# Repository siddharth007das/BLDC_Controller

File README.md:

# BLDC_Controller
A 50V 3Phase BLDC Controller Board designed to implement FoC Control of Hall Effect BLDC Motors such as NEMA17 24V 4000RPM. Utilizes Automotive grade Onsemi NFVA35065L32 Inverter ICs and STM32F4 to invert DC supply and perform Current and Voltage Measurement for FOC Control.

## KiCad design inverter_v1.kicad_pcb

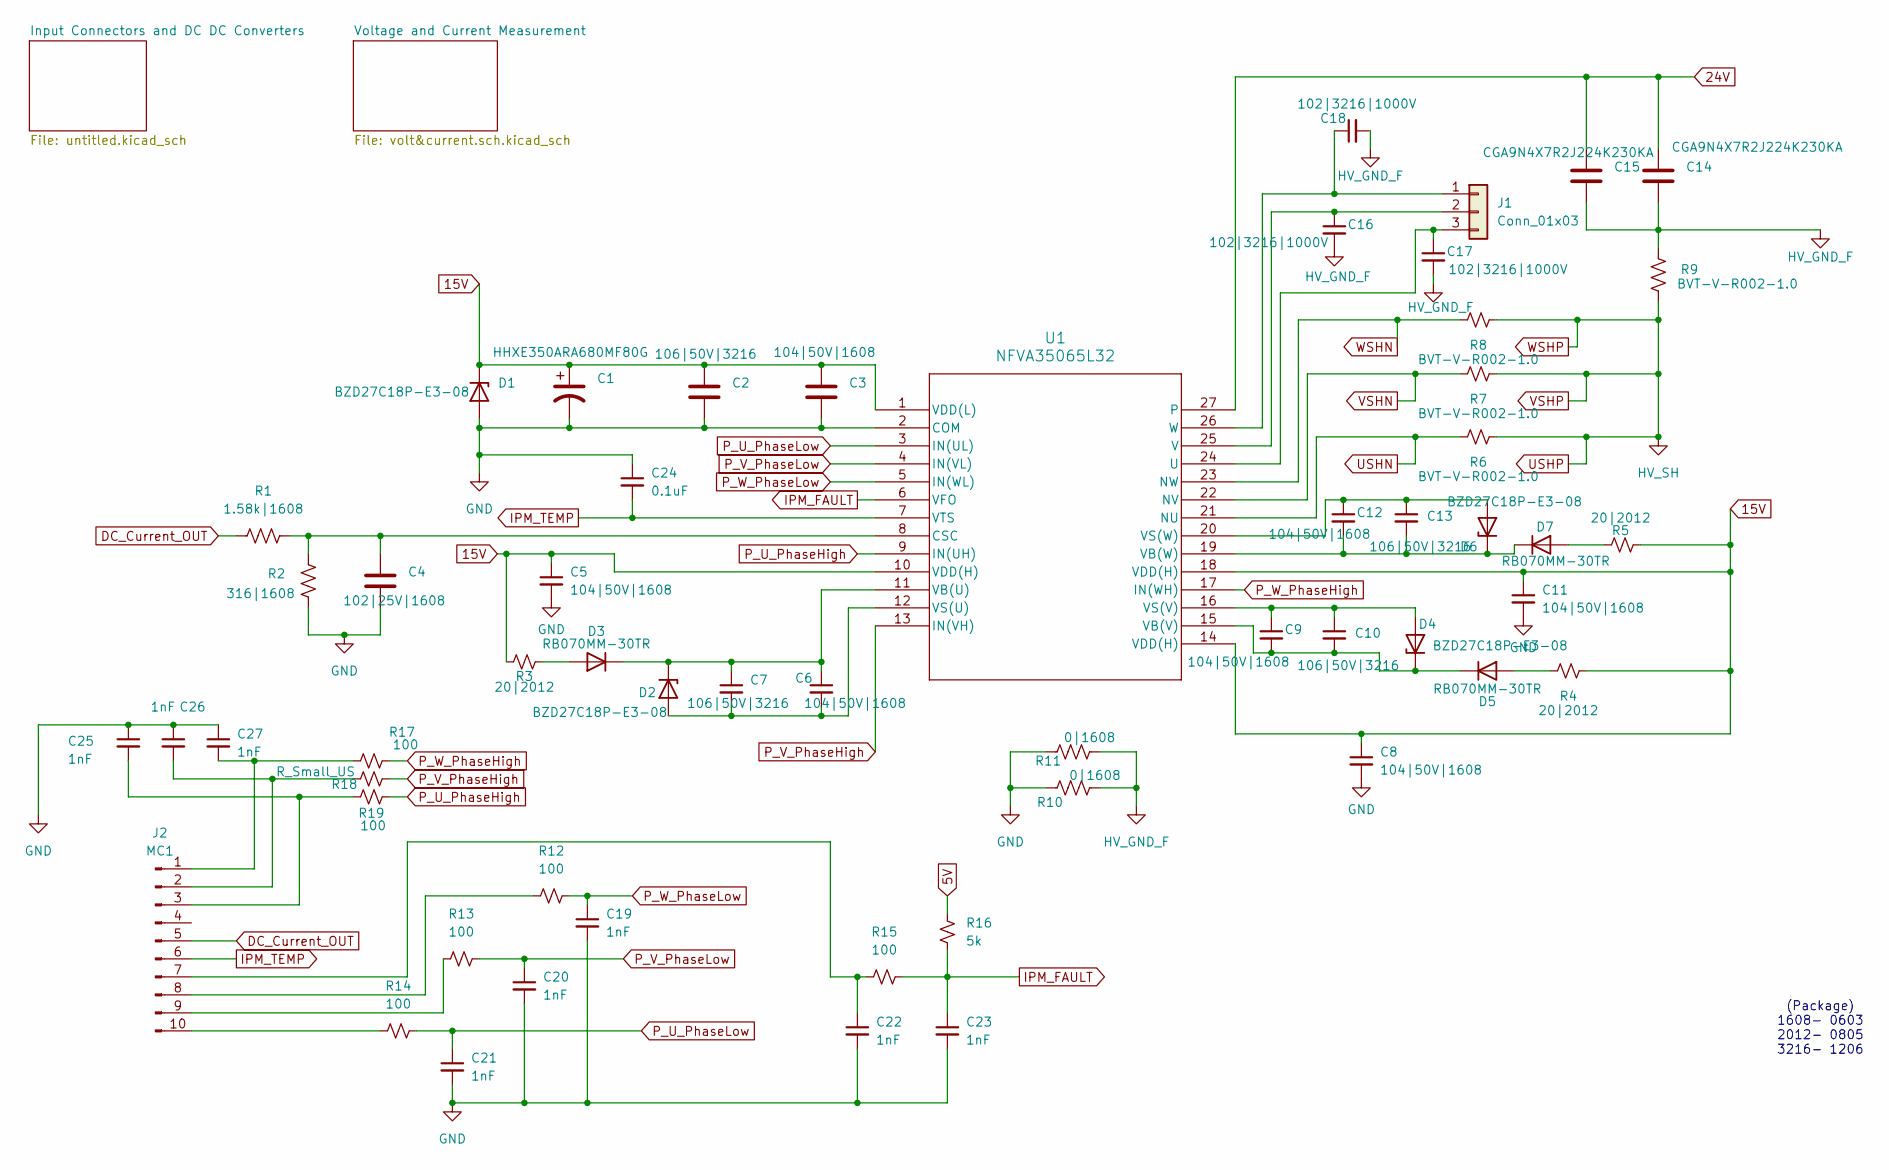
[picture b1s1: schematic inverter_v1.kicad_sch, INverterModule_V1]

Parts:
C1: HHXE350ARA680MF80G; CP_Elec_6.3x7.7
C2, C7, C10, C13: 106|50V|3216; C_1206_3216Metric
C3, C5, C6, C8, C9, C11, C12: 104|50V|1608; C_0603_1608Metric
C4: 102|25V|1608; C_0603_1608Metric
C14, C15: CGA9N4X7R2J224K230KA; C_2220_5750Metric
C16, C17, C18: 102|3216|1000V; C_1206_3216Metric
C19, C20, C21, C22, C23, C25, C26, C27: 1nF; C_0603_1608Metric
C24: 0.1uF; C_0603_1608Metric
D1, D2, D4, D6: BZD27C18P-E3-08; D_SMF
D3, D5, D7: RB070MM-30TR; D_SOD-123F
J1: Conn_01x03; TerminalBlock_Altech_AK300-3_P5.00mm
J2: MC1; PinHeader_1x10_P2.54mm_Vertical
R1: 1.58k|1608; R_0603_1608Metric
R2: 316|1608; R_0603_1608Metric
R3, R4, R5: 20|2012; R_0805_2012Metric
R6, R7, R8, R9: BVT-V-R002-1.0; R_2512_6332Metric
R10, R11: 0|1608; R_0603_1608Metric
R12, R13, R14, R15, R17, R19: 100; R_0603_1608Metric
R16: 5k; R_0603_1608Metric
R18: R_Small_US; R_0603_1608Metric
U1: NFVA35065L32; SPMBA-027_ONS

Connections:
5V: R16.2; also elsewhere on the board
15V: C1.1, C2.1, C3.1, C5.1, C8.1, C11.1, D1.1 (K), R3.1, R4.1, R5.1, U1.1 (VDD(L)), U1.10 (VDD(H)), U1.14 (VDD(H)), U1.18 (VDD(H)); also elsewhere on the board
DC_Current_OUT: J2.5, R1.1
GND: C1.2, C2.2, C3.2, C4.2, C5.2, C8.2, C11.2, C19.2, C20.2, C21.2, C22.2, C23.2, C24.1, C25.1, C26.1, C27.1, D1.2 (A), R2.1, R10.1, R11.1, U1.2 (COM); also elsewhere on the board
HV_Battery: C14.1, C15.1, U1.27; also elsewhere on the board
HV_GND_F: C14.2, C15.2, C16.2, C17.2, C18.2, R9.1, R10.2, R11.2; also elsewhere on the board
HV_SH: R6.1, R7.1, R8.1, R9.2; also elsewhere on the board
IPM_FAULT: C23.1, R15.2, R16.1, U1.6 (VFO)
IPM_TEMP: C24.2, J2.6, U1.7 (VTS)
unnamed: C6.2, C7.2, D2.2 (A), U1.12 (VS(U))
unnamed: C6.1, C7.1, D2.1 (K), D3.1 (K), U1.11 (VB(U))
unnamed: D3.2 (A), R3.2
unnamed: C9.1, C10.1, D4.2 (A), U1.16 (VS(V))
unnamed: C9.2, C10.2, D4.1 (K), D5.1 (K), U1.15 (VB(V))
unnamed: D5.2 (A), R4.2
unnamed: C12.1, C13.1, D6.2 (A), U1.20 (VS(W))
unnamed: C12.2, C13.2, D6.1 (K), D7.1 (K), U1.19 (VB(W))
unnamed: D7.2 (A), R5.2
unnamed: C18.1, J1.1, U1.26 (W)
unnamed: C16.1, J1.2, U1.25 (V)
unnamed: C17.1, J1.3, U1.24 (U)
unnamed: C27.2, J2.1, R17.1
unnamed: C26.2, J2.2, R18.1
unnamed: C25.2, J2.3, R19.1
unnamed: C22.1, J2.7, R15.1
unnamed: J2.8, R12.1
unnamed: J2.9, R13.1
unnamed: J2.10, R14.1
unnamed: C4.1, R1.2, R2.2, U1.8 (CSC)
unnamed: R6.2, U1.21 (NU)
unnamed: R7.2, U1.22 (NV)
unnamed: R8.2, U1.23 (NW)
P_U_PhaseHigh: R19.2, U1.9 (IN(UH))
P_U_PhaseLow: C21.1, R14.2, U1.3 (IN(UL))
P_V_PhaseHigh: R18.2, U1.13 (IN(VH))
P_V_PhaseLow: C20.1, R13.2, U1.4 (IN(VL))
P_W_PhaseHigh: R17.2, U1.17 (IN(WH))
P_W_PhaseLow: C19.1, R12.2, U1.5 (IN(WL))

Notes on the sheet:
(Package) 1608- 0603 2012- 0805 3216- 1206

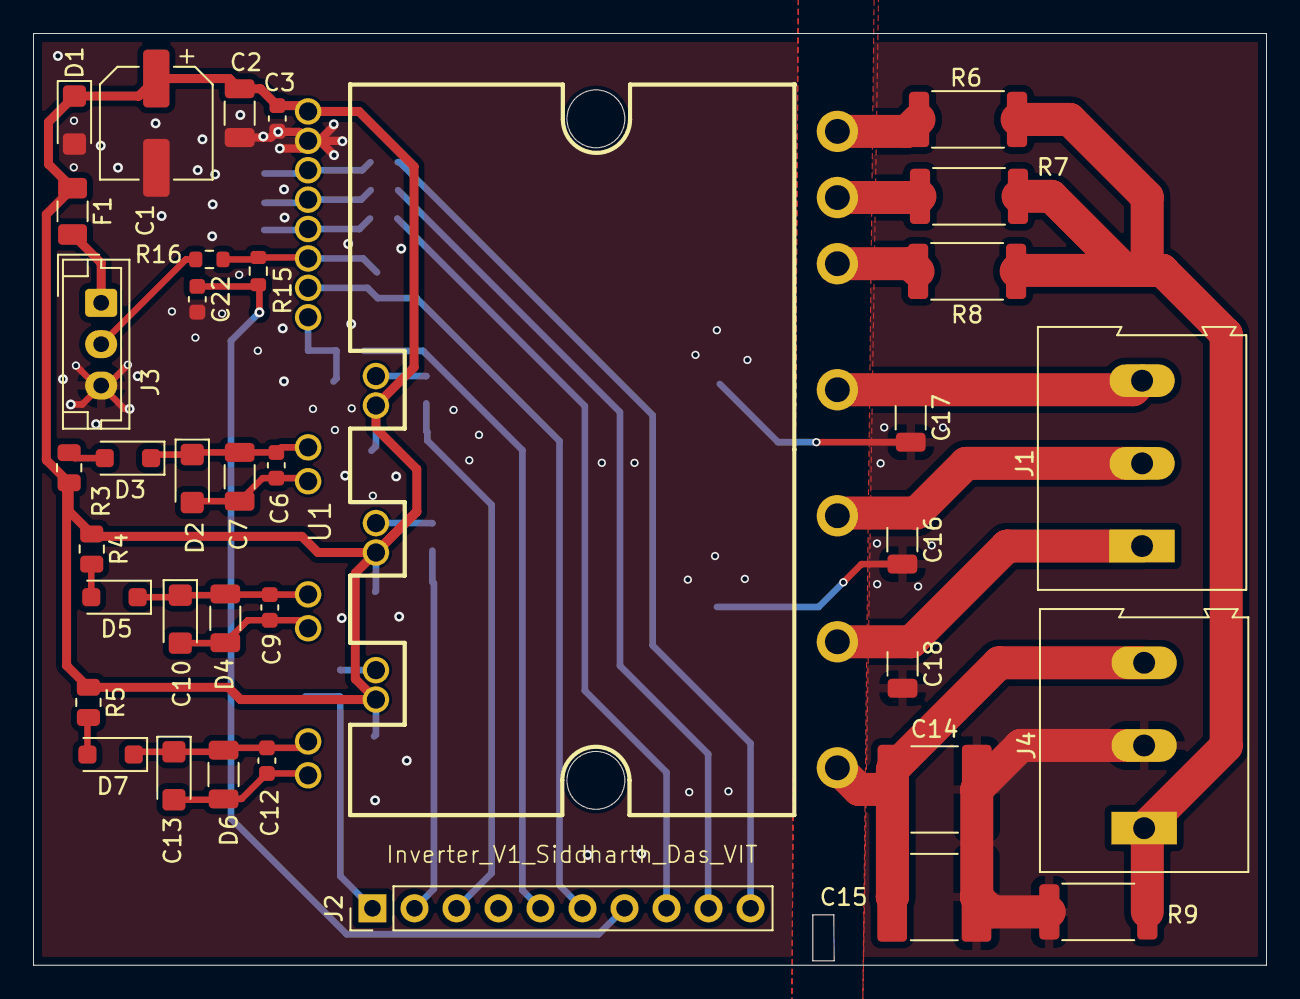
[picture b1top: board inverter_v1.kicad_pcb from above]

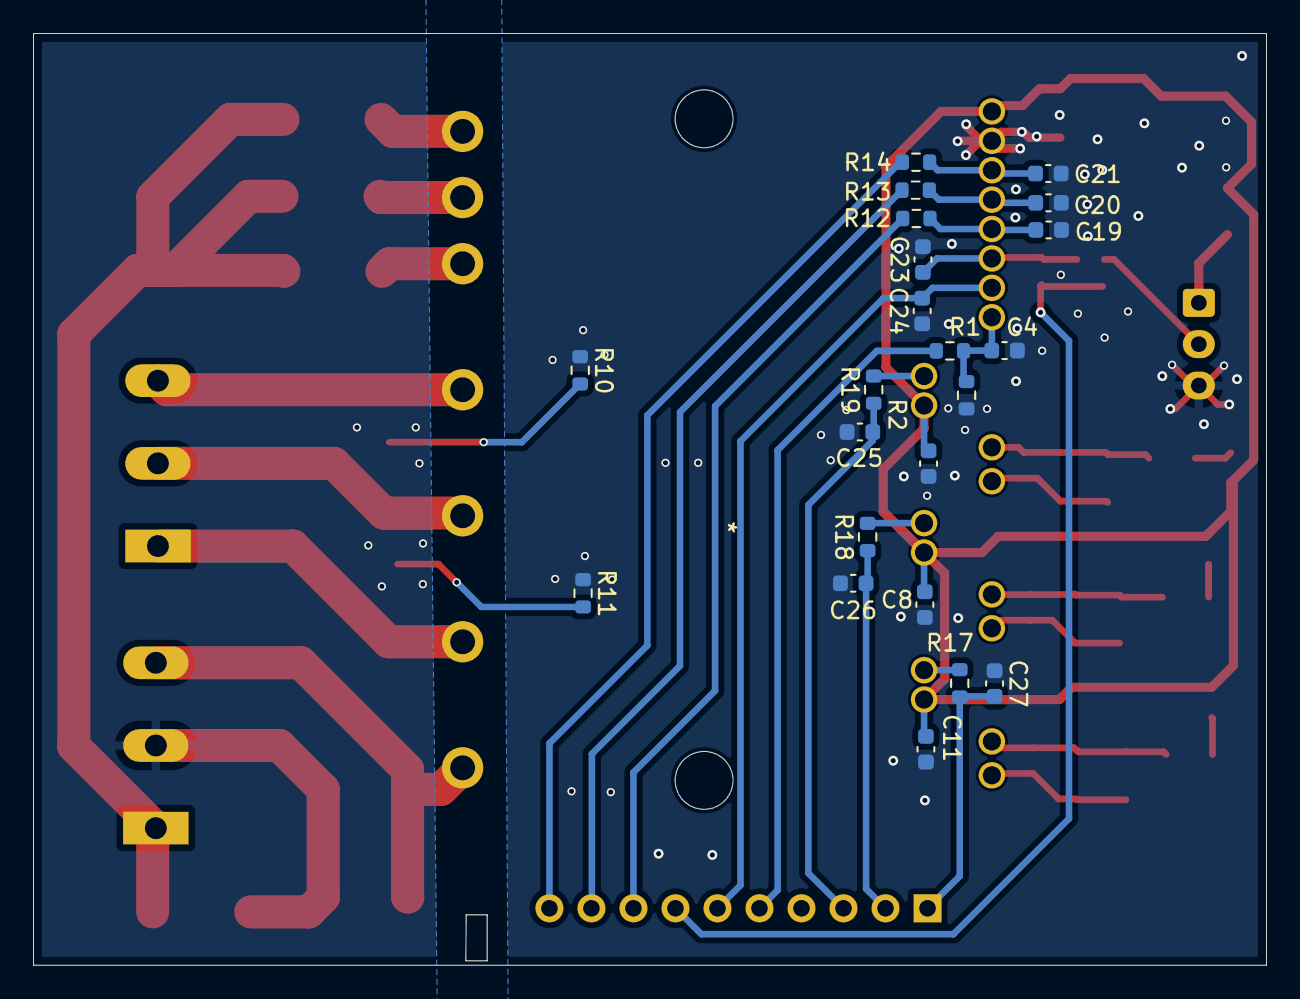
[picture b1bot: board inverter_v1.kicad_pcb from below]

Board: 2 copper layers, 74.6 x 56.3 mm, 59 parts (22 on the bottom side), 39 nets.

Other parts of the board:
F1: Fuse; Fuse_1206_3216Metric
J3: PWR_LV; JST_EH_B3B-EH-A_1x03_P2.50mm_Vertical
J4: PWR_HW; TerminalBlock_Altech_AK300-3_P5.00mm

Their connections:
5V: J3.2; also elsewhere on the board
15V: F1.1; also elsewhere on the board
GND: J3.3; also elsewhere on the board
HV_Battery: J4.3; also elsewhere on the board
HV_GND_F: J4.2; also elsewhere on the board
HV_SH: J4.1; also elsewhere on the board
unnamed: F1.2, J3.1
